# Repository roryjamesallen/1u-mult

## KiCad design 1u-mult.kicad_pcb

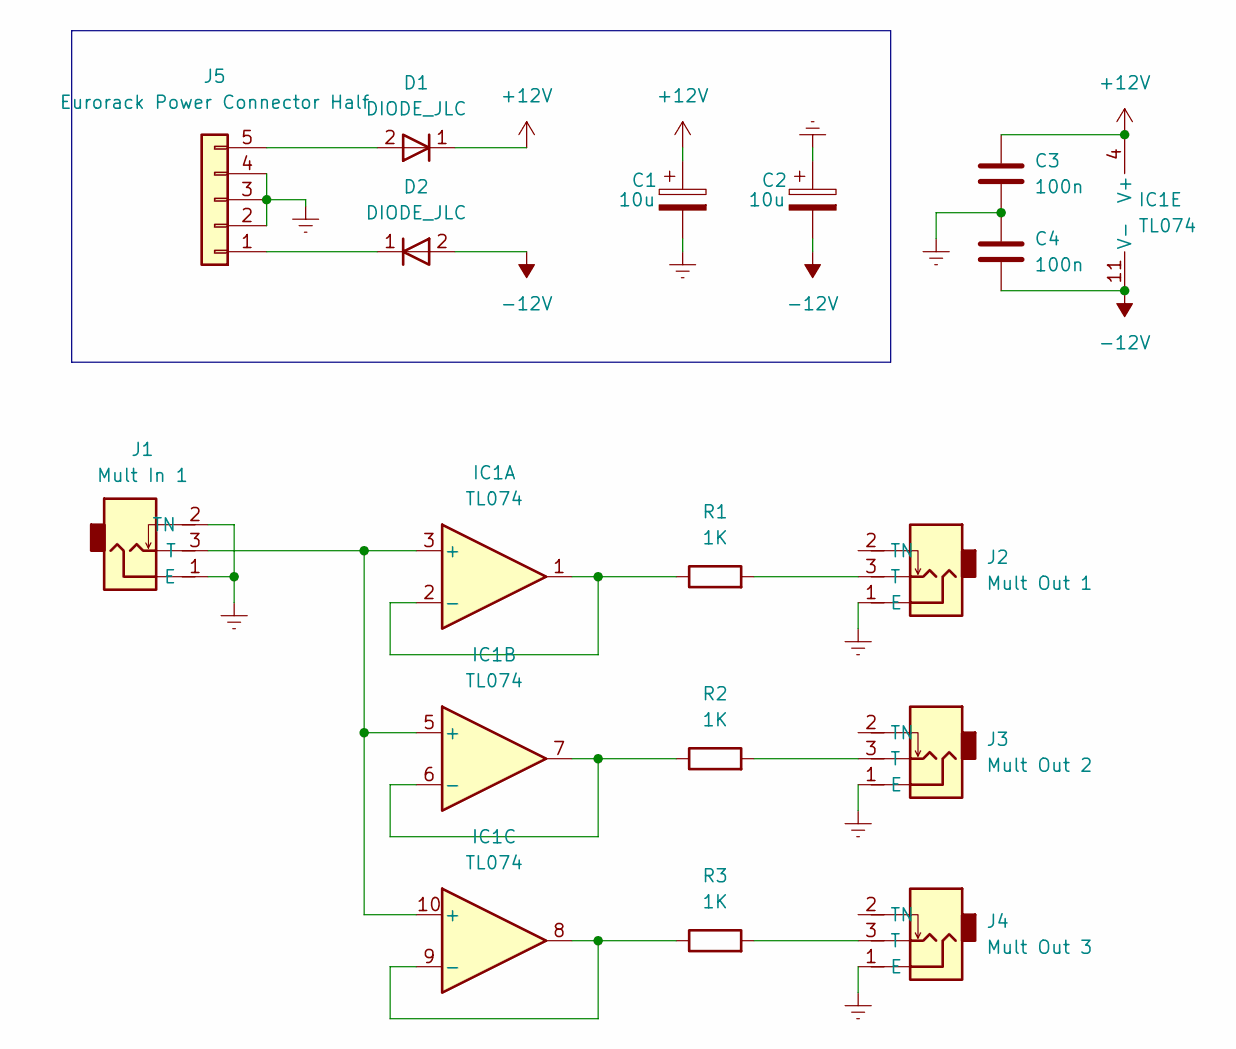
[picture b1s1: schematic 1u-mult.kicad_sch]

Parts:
C1, C2: 10u; C_0805_2012Metric
C3, C4: 100n; C_0805_2012Metric
D1, D2: DIODE_JLC; D_SMA
IC1: TL074; SOIC-14_3.9x8.7mm_P1.27mm
J1: Mult In 1; Thonkiconn Mono Jack
J2: Mult Out 1; Thonkiconn Mono Jack
J3: Mult Out 2; Thonkiconn Mono Jack
J4: Mult Out 3; Thonkiconn Mono Jack
J5: Eurorack Power Connector Half; Eurorack Power Header Unlabeled Half
R1, R2, R3: 1K; R_0805_2012Metric

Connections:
+12V: C1.1, C3.1, D1.1 (A), IC1.4 (V+)
-12V: C2.2, C4.2, D2.2 (K), IC1.11 (V-)
Earth: C1.2, C2.1, C3.2, C4.1, J1.1 (E), J1.2 (TN), J2.1 (E), J3.1 (E), J4.1 (E), J5.2, J5.3, J5.4
unnamed: IC1.3 (+), IC1.5 (+), IC1.10 (+), J1.3 (T)
unnamed: J2.3 (T), R1.2
unnamed: J3.3 (T), R2.2
unnamed: J4.3 (T), R3.2
unnamed: D2.1 (A), J5.1
unnamed: D1.2 (K), J5.5
unnamed: IC1.1, IC1.2 (-), R1.1
unnamed: IC1.6 (-), IC1.7, R2.1
unnamed: IC1.8, IC1.9 (-), R3.1

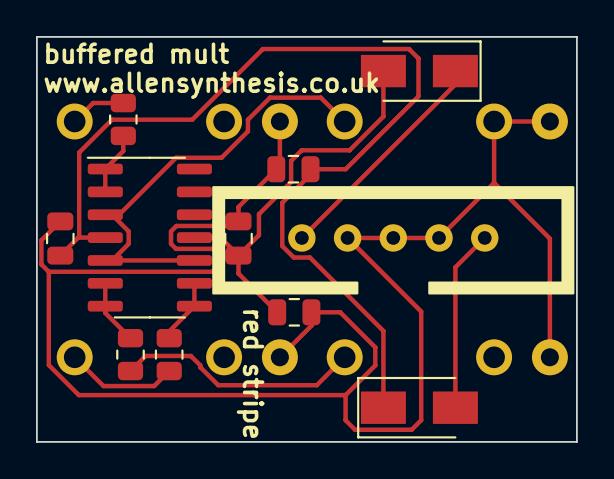
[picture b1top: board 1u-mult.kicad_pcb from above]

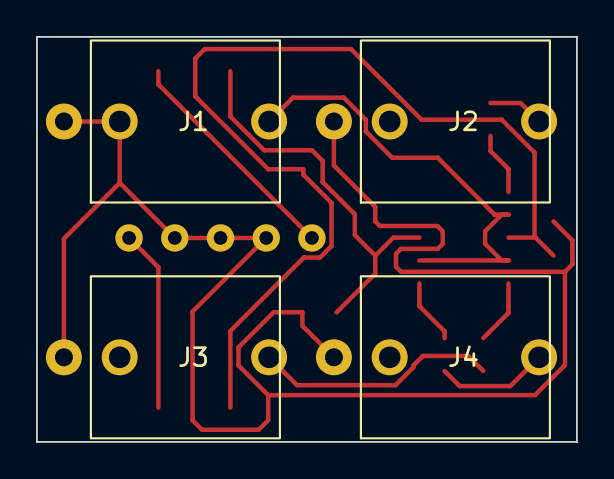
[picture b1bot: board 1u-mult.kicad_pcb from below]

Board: 2 copper layers, 30.0 x 22.5 mm, 15 parts (4 on the bottom side), 12 nets.

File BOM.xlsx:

Comment | Designator | Footprint | JLCPCB Part #（optional）
Diode | D1,D2 | D_SMA | C95872
Tl074 | IC1 | SOIC-14_3.9x8.7mm_P1.27mm | C12594
10u | C1,C2 | C_0805_2012Metric | C15850
100n | C3,C4 | C_0805_2012Metric | C49678
1k | R1,R2,R3 | R_0805_2012Metric | C17513

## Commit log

2022-05-15 Enlarge holes, add mounting holes, add silkscreen in/out markings
